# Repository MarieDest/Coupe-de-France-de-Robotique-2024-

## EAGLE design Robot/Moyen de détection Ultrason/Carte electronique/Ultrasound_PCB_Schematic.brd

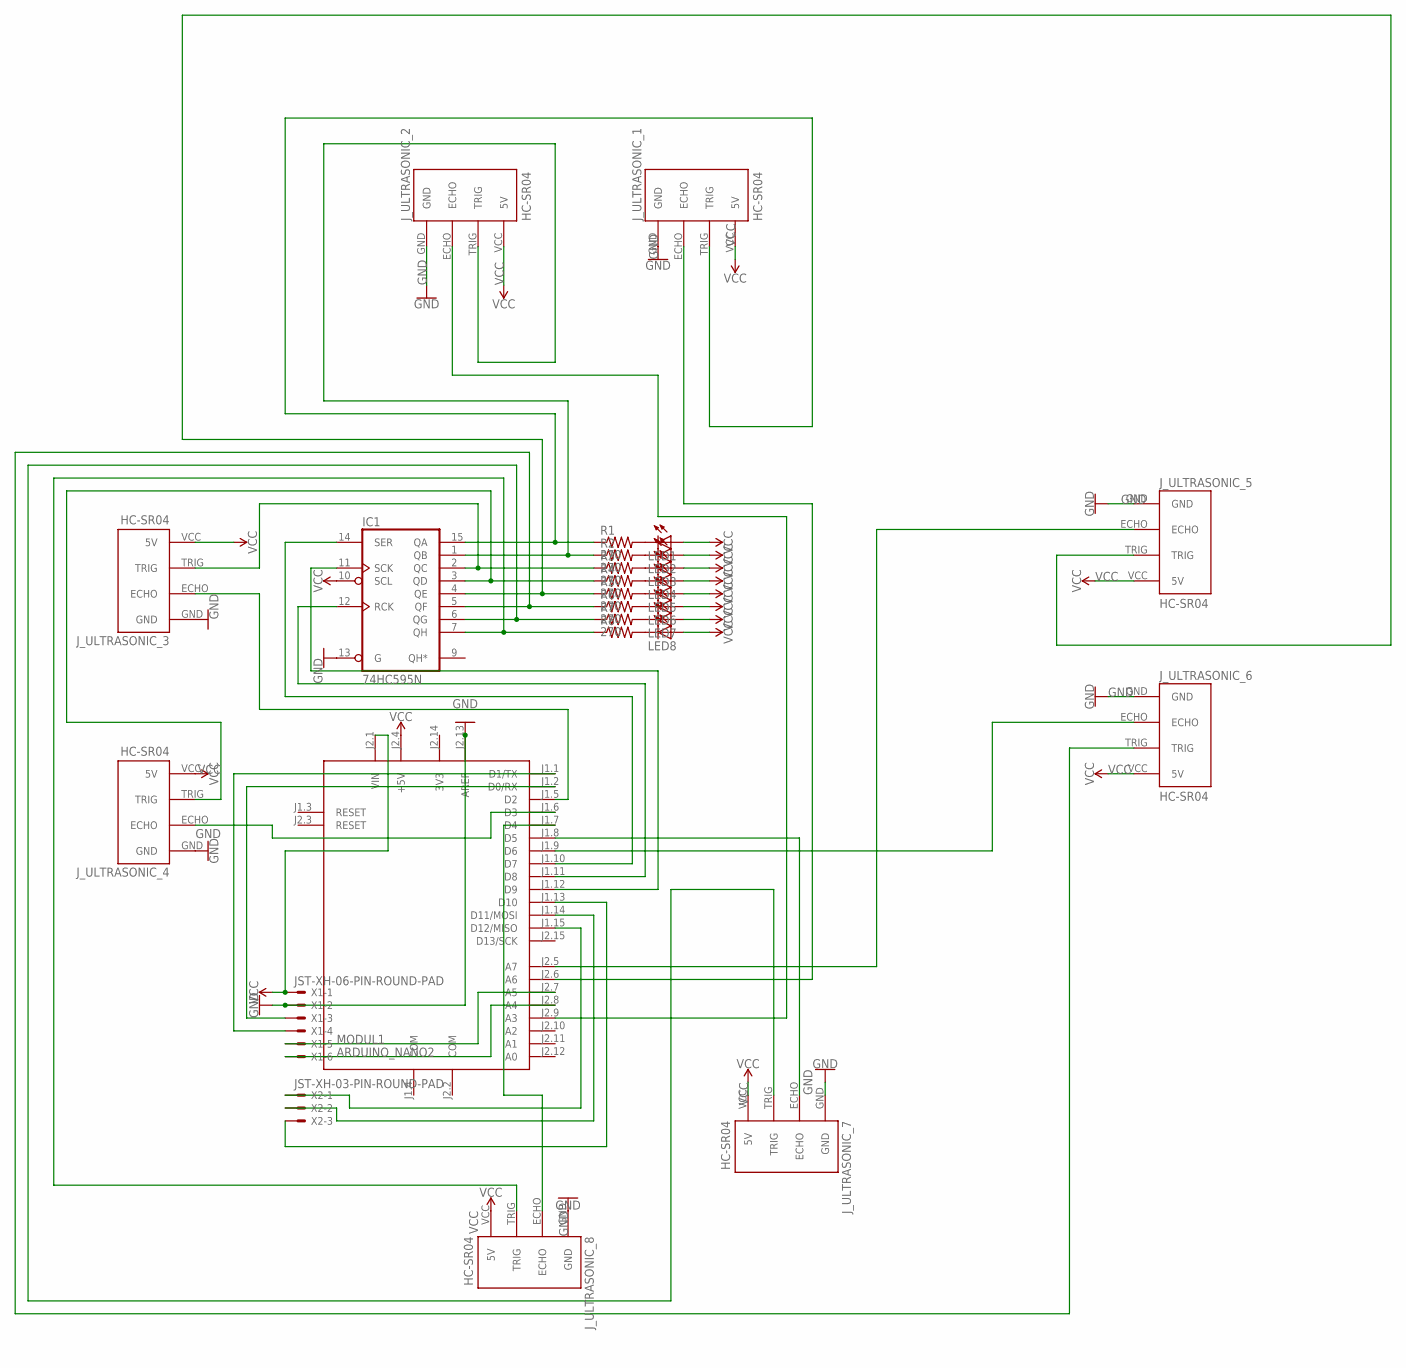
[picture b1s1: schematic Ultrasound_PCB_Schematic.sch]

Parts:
IC1: 74HC595N; DIL16
J_ULTRASONIC_1, J_ULTRASONIC_2, J_ULTRASONIC_3, J_ULTRASONIC_4, J_ULTRASONIC_5, J_ULTRASONIC_6, J_ULTRASONIC_7, J_ULTRASONIC_8: HC-SR04; HC-SR04_FOOTPRINT
LED1, LED2, LED3, LED4, LED5, LED6, LED7, LED8: LED5MM
MODUL1: ARDUINO_NANO2
R1, R2, R3, R4, R5, R6, R7: 270; 0207/5V
R8: R-US_0207/5V; 0207/5V
X1: JST-XH-06-PIN-ROUND-PAD; JST-XH-06-PACKAGE-ROUND-PAD
X2: JST-XH-03-PIN-ROUND-PAD; JST-XH-03-PACKAGE-ROUND-PAD

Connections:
3V3: MODUL1.J2.14 (3V3)
COM: MODUL1.J1.4 (COM), MODUL1.J2.2 (COM)
GND: IC1.8 (GND), IC1.13 (G), J_ULTRASONIC_1.GND, J_ULTRASONIC_2.GND, J_ULTRASONIC_3.GND, J_ULTRASONIC_4.GND, J_ULTRASONIC_5.GND, J_ULTRASONIC_6.GND, J_ULTRASONIC_7.GND, J_ULTRASONIC_8.GND, MODUL1.J2.13 (AREF), X1.2
IC1_A_SCL: IC1.11 (SCK), MODUL1.J1.12 (D9)
unnamed: J_ULTRASONIC_2.ECHO, MODUL1.J2.9 (A3)
unnamed: J_ULTRASONIC_1.ECHO, MODUL1.J2.6 (A6)
unnamed: J_ULTRASONIC_5.ECHO, MODUL1.J2.5 (A7)
unnamed: J_ULTRASONIC_6.ECHO, MODUL1.J1.9 (D6)
unnamed: J_ULTRASONIC_3.ECHO, MODUL1.J1.5 (D2)
unnamed: J_ULTRASONIC_8.ECHO, MODUL1.J1.7 (D4)
unnamed: J_ULTRASONIC_4.ECHO, MODUL1.J1.6 (D3)
unnamed: J_ULTRASONIC_7.ECHO, MODUL1.J1.8 (D5)
unnamed: LED8.K (C), R8.2
unnamed: IC1.1 (QB), J_ULTRASONIC_2.TRIG, R2.1
unnamed: IC1.15 (QA), J_ULTRASONIC_1.TRIG, R1.1
unnamed: IC1.3 (QD), J_ULTRASONIC_4.TRIG, R4.1
unnamed: IC1.7 (QH), J_ULTRASONIC_8.TRIG, R8.1
unnamed: IC1.6 (QG), J_ULTRASONIC_7.TRIG, R7.1
unnamed: IC1.5 (QF), J_ULTRASONIC_6.TRIG, R6.1
unnamed: IC1.4 (QE), J_ULTRASONIC_5.TRIG, R5.1
unnamed: IC1.14 (SER), MODUL1.J1.10 (D7)
unnamed: IC1.12 (RCK), MODUL1.J1.11 (D8)
unnamed: LED7.K (C), R7.2
unnamed: LED6.K (C), R6.2
unnamed: LED5.K (C), R5.2
unnamed: LED4.K (C), R4.2
unnamed: MODUL1.J1.1 (D1/TX), X1.4
unnamed: MODUL1.J1.2 (D0/RX), X1.3
unnamed: MODUL1.J2.7 (A5), X1.5
unnamed: MODUL1.J2.8 (A4), X1.6
unnamed: MODUL1.J1.15 (D12/MISO), X2.1
unnamed: MODUL1.J1.14 (D11/MOSI), X2.2
unnamed: MODUL1.J1.13 (D10), X2.3
unnamed: LED3.K (C), R3.2
unnamed: LED2.K (C), R2.2
unnamed: LED1.K (C), R1.2
unnamed: IC1.2 (QC), J_ULTRASONIC_3.TRIG, R3.1
VCC: IC1.10 (SCL), IC1.16 (VCC), J_ULTRASONIC_1.VCC (5V), J_ULTRASONIC_2.VCC (5V), J_ULTRASONIC_3.VCC (5V), J_ULTRASONIC_4.VCC (5V), J_ULTRASONIC_5.VCC (5V), J_ULTRASONIC_6.VCC (5V), J_ULTRASONIC_7.VCC (5V), J_ULTRASONIC_8.VCC (5V), LED1.A, LED2.A, LED3.A, LED4.A, LED5.A, LED6.A, LED7.A, LED8.A, MODUL1.J2.1 (VIN), MODUL1.J2.4 (+5V), X1.1

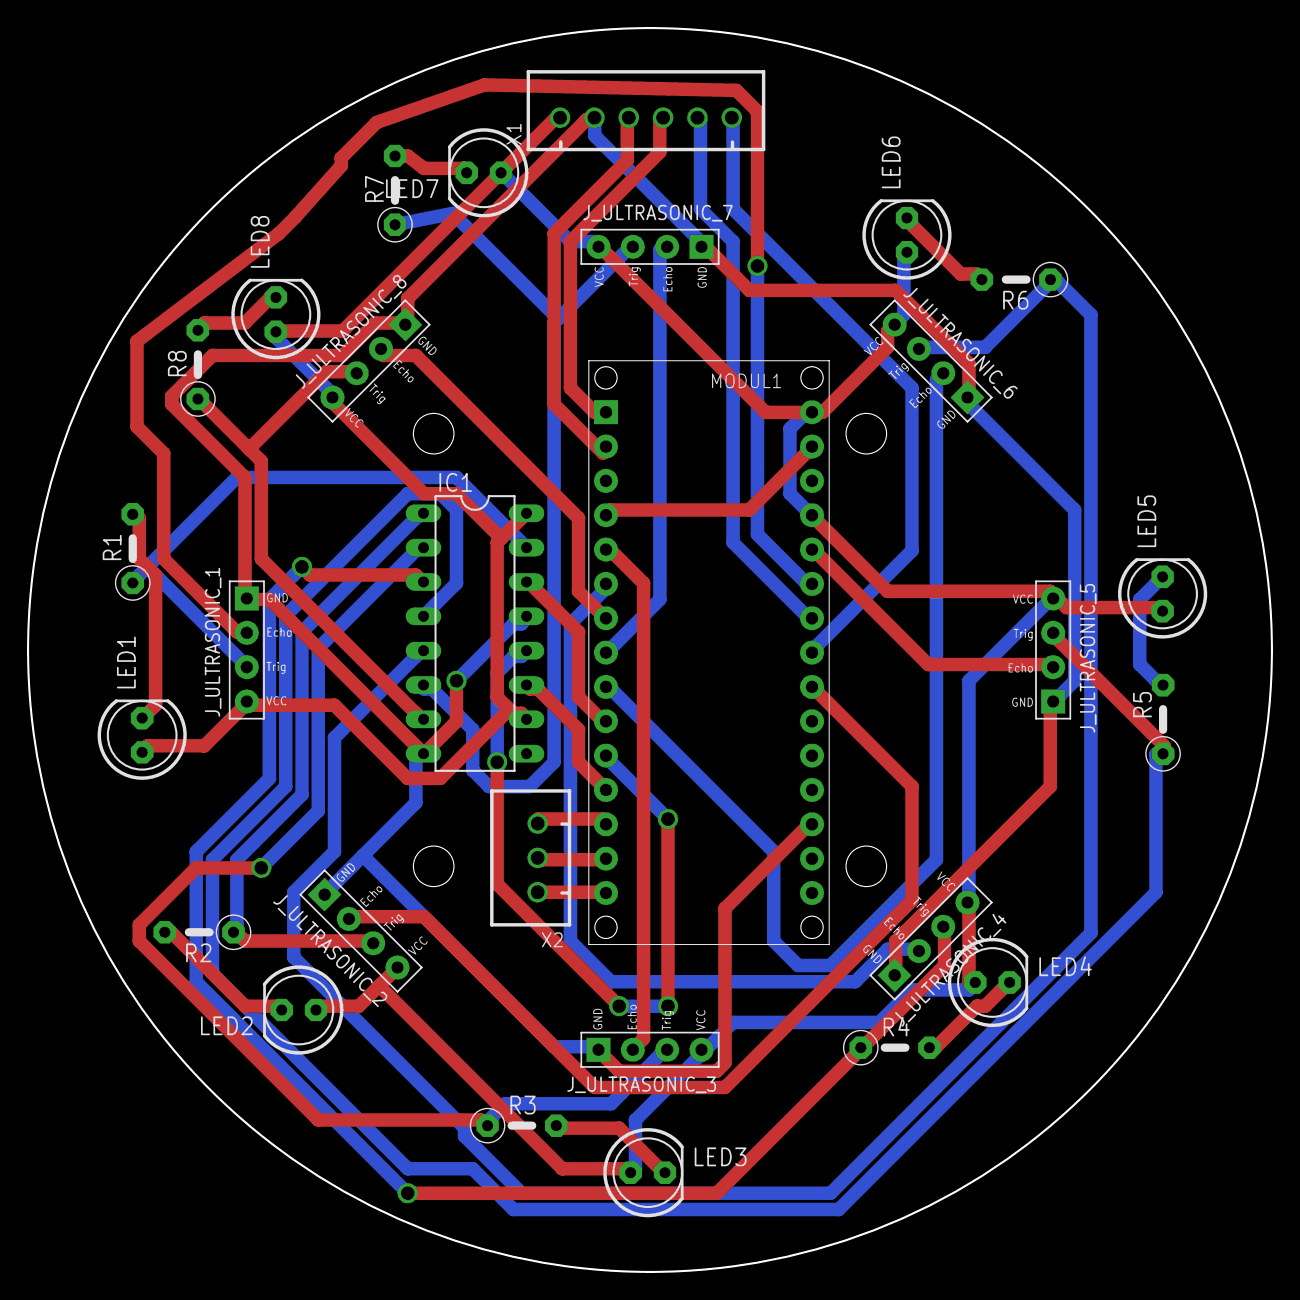
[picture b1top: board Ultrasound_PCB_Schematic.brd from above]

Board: 2 copper layers, 92.0 x 92.0 mm, 28 parts (0 on the bottom side), 37 nets.

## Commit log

2023-09-24 Ajout du fichier STL de la base Robot 2024
    Fichier SolidWorks
2023-10-03 Ajout modèle 3D du PAMI et des dossiers robots et PAMI
2023-12-29 Ajout des fichiers de création de la carte electronique ainsi que du programme de controle de 8 ultrasons tour a tour
    Tous les fichiers nécessaires à la création et à la production (en chine) de la carte électronique avec 8 ultrasons
    Le code qui permet de faire fonctionner ces 8 ultrasons.
2024-01-02 Nouvelle version des fichiers
    la nouvelle version est due au fait que l'ancienne était trop grande, eh oui, un carré de 8cm a une diagonale de 11.3 cm (supérieur au 10cm max😭) par conséquent, j'ai créé un nouveau design, qui conv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
2024-01-21 Ultrasons avec la com I2C fonctionnelle V1
    le programme de la carte principale et de la carte secondaire ultrasons
2024-05-06 Ajout Code carte Principale
2024-05-13 code en fin de coupe 2024
    va chercher des panneaux solaires et les tourne

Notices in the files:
parts and their libraries:
SparkFun-PowerSymbols: Licensing: Creative Commons ShareAlike 4.0 International - https://creativecommons.org/licenses/by-sa/4.0
